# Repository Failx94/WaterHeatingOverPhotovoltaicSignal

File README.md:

# WaterHeatingOverPhotovoltaicSignal
*WIP*

## Other used Projects:

https://www.thingiverse.com/thing:500504

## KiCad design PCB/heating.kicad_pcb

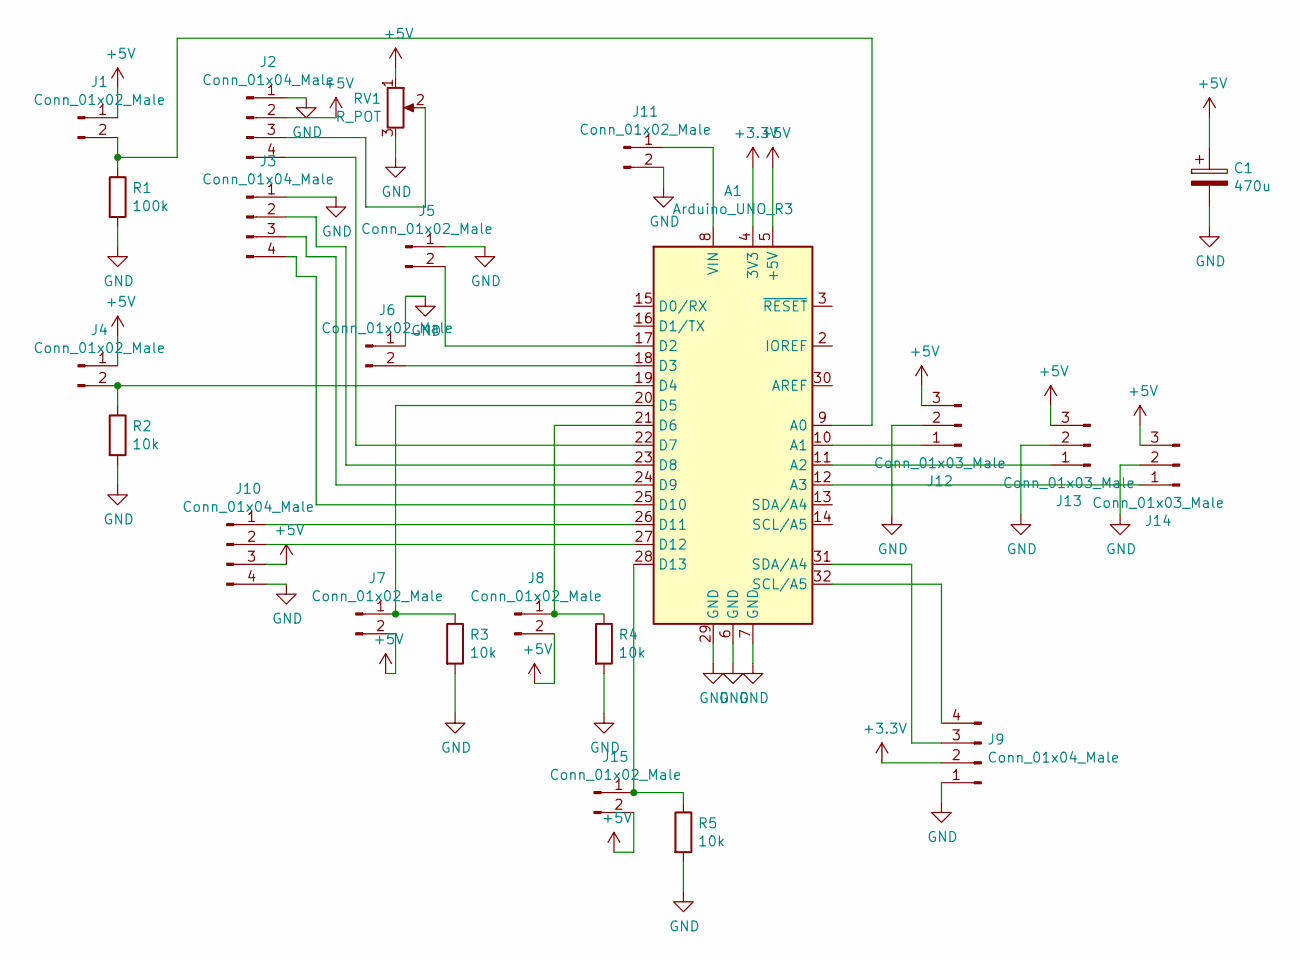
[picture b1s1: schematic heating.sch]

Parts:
A1: Arduino_UNO_R3
C1: 470u; CP_Radial_D10.0mm_P5.00mm
J1, J5, J6, J7, J8, J15: Conn_01x02_Male; JST_EH_B2B-EH-A_1x02_P2.50mm_Vertical
J2, J3: Conn_01x04_Male; PinHeader_1x04_P2.54mm_Horizontal
J4, J11: Conn_01x02_Male; TerminalBlock_bornier-2_P5.08mm
J9, J10: Conn_01x04_Male; PinSocket_1x04_P2.54mm_Horizontal
J12, J13, J14: Conn_01x03_Male; JST_EH_B3B-EH-A_1x03_P2.50mm_Vertical
R1: 100k; R_Axial_DIN0411_L9.9mm_D3.6mm_P12.70mm_Horizontal
R2, R3, R4, R5: 10k; R_Axial_DIN0411_L9.9mm_D3.6mm_P12.70mm_Horizontal
RV1: R_POT; Potentiometer_Piher_PT-15-V02_Vertical

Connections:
+3V3: A1.4 (3V3), J9.2
+5V: A1.5 (+5V), C1.1, J1.1, J2.2, J4.1, J7.2, J8.2, J10.3, J12.3, J13.3, J14.3, J15.2, RV1.1
GND: A1.6 (GND), A1.7 (GND), A1.29 (GND), C1.2, J2.1, J3.1, J5.1, J6.1, J9.1, J10.4, J11.2, J12.2, J13.2, J14.2, R1.2, R2.2, R3.2, R4.2, R5.2, RV1.3
unnamed: A1.8 (VIN), J11.1
unnamed: A1.9 (A0), J1.2, R1.1
unnamed: A1.10 (A1), J12.1
unnamed: A1.11 (A2), J13.1
unnamed: A1.12 (A3), J14.1
unnamed: A1.17 (D2), J5.2
unnamed: A1.18 (D3), J6.2
unnamed: A1.19 (D4), J4.2, R2.1
unnamed: A1.20 (D5), J7.1, R3.1
unnamed: A1.21 (D6), J8.1, R4.1
unnamed: A1.22 (D7), J2.4
unnamed: A1.23 (D8), J3.2
unnamed: A1.24 (D9), J3.3
unnamed: A1.25 (D10), J3.4
unnamed: A1.26 (D11), J10.1
unnamed: A1.27 (D12), J10.2
unnamed: A1.28 (D13), J15.1, R5.1
unnamed: A1.31 (SDA/A4), J9.3
unnamed: A1.32 (SCL/A5), J9.4
unnamed: J2.3, RV1.2

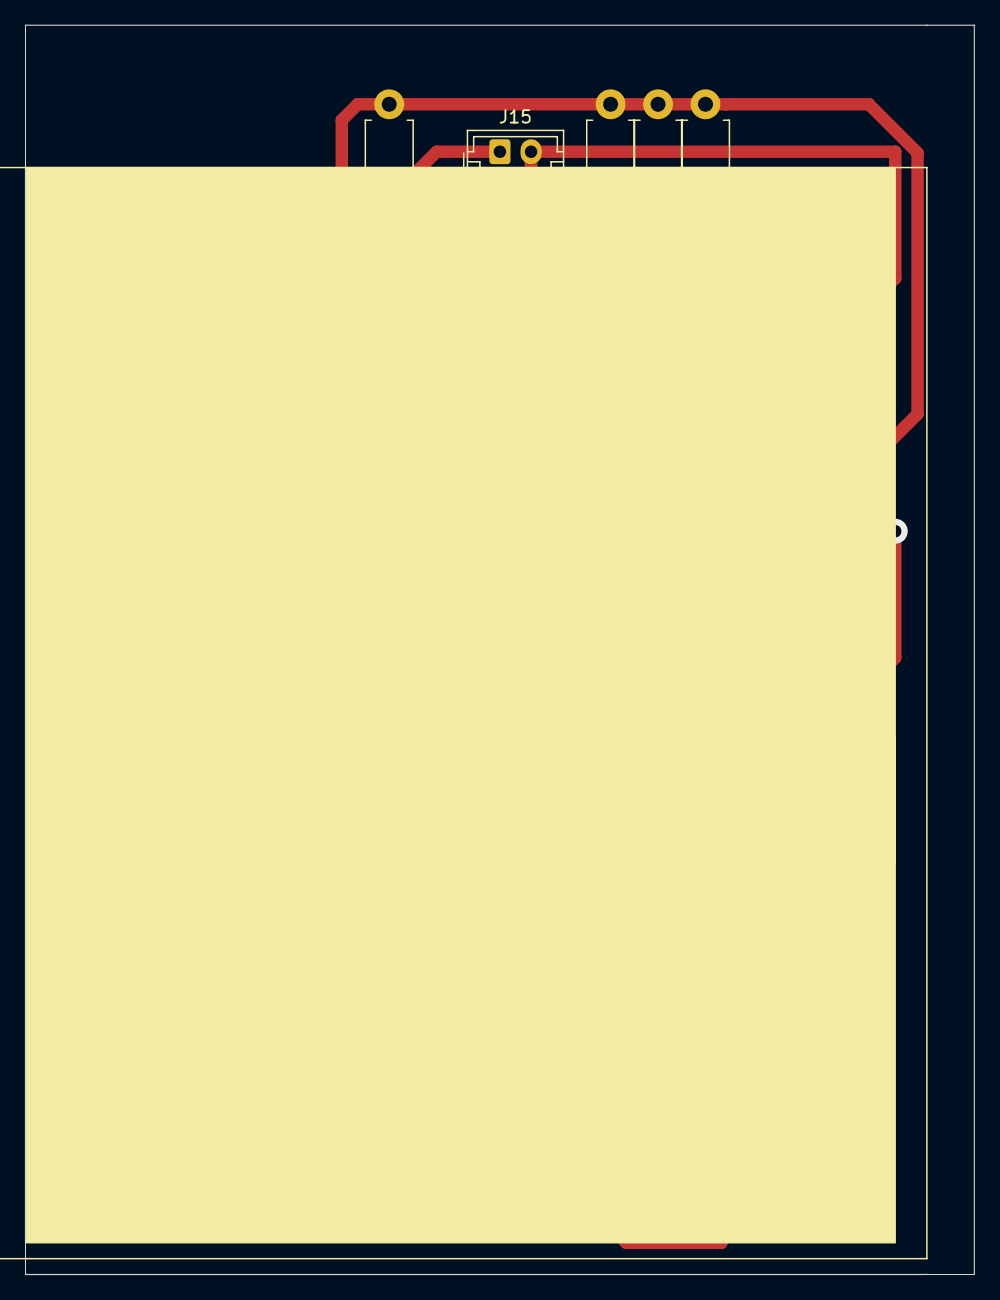
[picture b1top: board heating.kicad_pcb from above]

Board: 2 copper layers, 76.2 x 100.3 mm, 23 parts (1 on the bottom side), 23 nets.

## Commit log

2020-05-07 Init
2020-05-08 Add new STLs
2020-05-09 Update PCB Layout
2020-05-09 PCB Overview
2020-05-09 Adding Button Mount STL
2020-05-15 Update PCB
2020-05-17 Change Pindefinitions
